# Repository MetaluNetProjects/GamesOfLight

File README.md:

# GamesOfLight
GroupeLAPS - GamesOfLight repository

### Pd externals to install:

- Fraise
- moonlib
- zexy
- ggee
- motex
- iemlib

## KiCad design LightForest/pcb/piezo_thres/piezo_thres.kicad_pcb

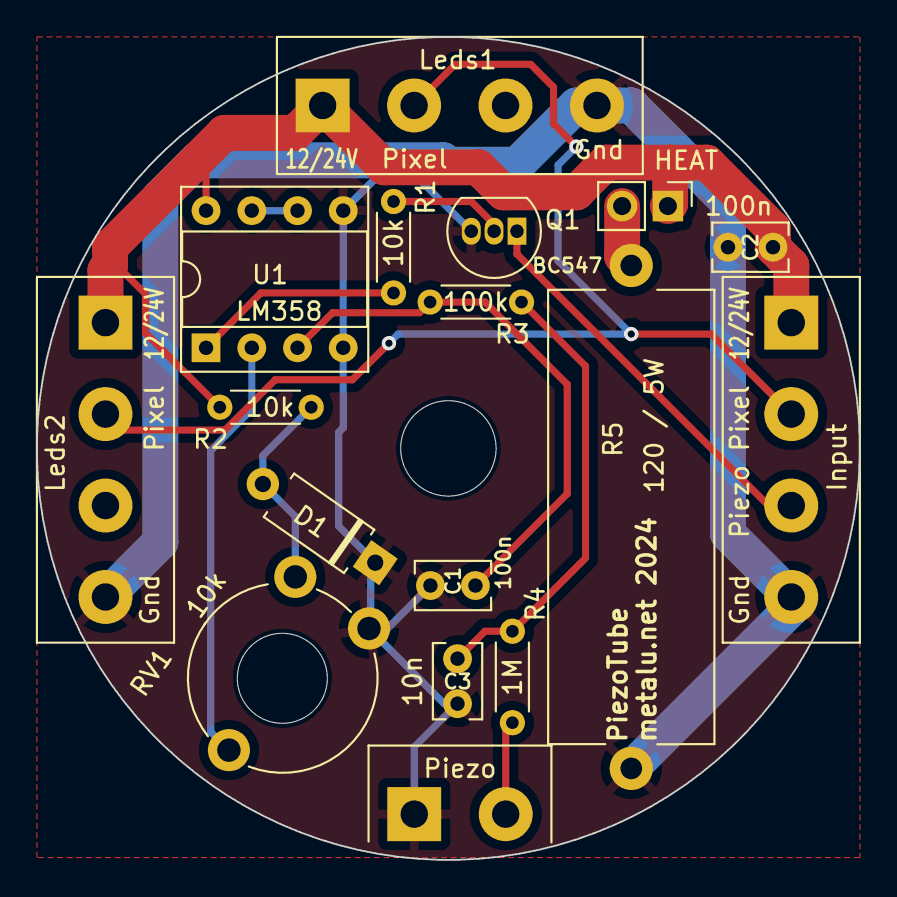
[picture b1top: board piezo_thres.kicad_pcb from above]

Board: 2 copper layers, 45.7 x 45.7 mm, 18 parts (0 on the bottom side), 13 nets.

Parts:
C1, C2: 100n; C_Rect_L4.0mm_W2.5mm_P2.50mm
C3: 10n; C_Rect_L4.0mm_W2.5mm_P2.50mm
D1: D; D_A-405_P7.62mm_Horizontal
H2: MountingHole; MountingHole_5.3mm_M5
HEAT: Conn_01x02_Pin; PinHeader_1x02_P2.54mm_Vertical
J1: Piezo; TerminalBlock_bornier-2_P5.08mm
J2: Input; TerminalBlock_bornier-4_P5.08mm
J3: Leds1; TerminalBlock_bornier-4_P5.08mm
J4: Leds2; TerminalBlock_bornier-4_P5.08mm
Q1: BC547; TO-92_Inline
R1, R2: 10k; R_Axial_DIN0204_L3.6mm_D1.6mm_P5.08mm_Horizontal
R3: 100k; R_Axial_DIN0204_L3.6mm_D1.6mm_P5.08mm_Horizontal
R4: 1M; R_Axial_DIN0204_L3.6mm_D1.6mm_P5.08mm_Horizontal
R5: 120 / 5W; R_Axial_Power_L25.0mm_W9.0mm_P27.94mm
RV1: 10k; Potentiometer_Piher_PT-10-V10_Vertical
U1: LM358; DIP-8_W7.62mm_Socket

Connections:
+24V: C2.1, HEAT.1, J2.1, J3.1, J4.1, R2.1, U1.8 (V+)
/piezo_out: J2.3, Q1.1 (C)
/pixel: J2.2, J3.2, J4.2
GND: C1.2, C2.2, C3.2, D1.1 (K), J1.1, J2.4, J3.4, J4.4, Q1.3 (E), R5.1, RV1.3, U1.4 (V-), U1.5 (+)
unnamed: C3.1, R3.2, R4.1
unnamed: D1.2 (A), R2.2, RV1.1
unnamed: J1.2, R4.2
unnamed: HEAT.2, R5.2
unnamed: Q1.2 (B), R1.2
unnamed: R1.1, U1.1
unnamed: C1.1, R3.1, U1.3 (+)
unnamed: RV1.2, U1.2 (-)
unnamed: U1.6 (-), U1.7

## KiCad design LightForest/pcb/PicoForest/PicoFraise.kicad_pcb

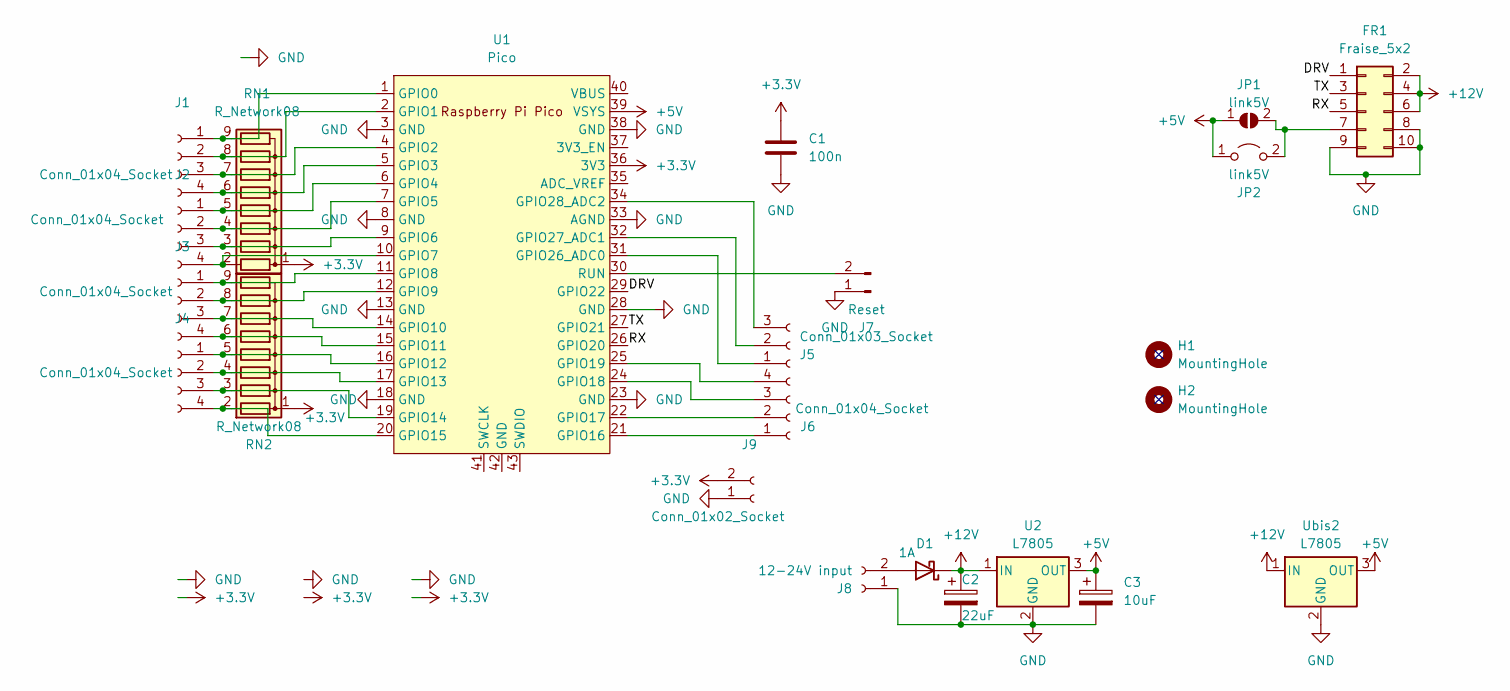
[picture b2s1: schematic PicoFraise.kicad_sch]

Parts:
C1: 100n; C_Rect_L4.0mm_W2.5mm_P2.50mm
C2: 22uF; CP_Radial_D5.0mm_P2.50mm
C3: 10uF; CP_Radial_D5.0mm_P2.50mm
D1: 1A; D_SMA
FR1: Fraise_5x2; IDC-Header_2x05_P2.54mm_Vertical
H1, H2: MountingHole; MountingHole_3.2mm_M3_Pad_TopOnly
J1, J2, J3, J4, J6: Conn_01x04_Socket; TerminalBlock_bornier-4_P5.08mm
J5: Conn_01x03_Socket; TerminalBlock_bornier-3_P5.08mm
J7: Reset; PinHeader_1x02_P2.54mm_Vertical
J8: 12-24V input; TerminalBlock_bornier-2_P5.08mm
J9: Conn_01x02_Socket; TerminalBlock_bornier-2_P5.08mm
JP1: link5V; SolderJumper-2_P1.3mm_Open_RoundedPad1.0x1.5mm
JP2: link5V; TestPoint_2Pads_Pitch2.54mm_Drill0.8mm
RN1, RN2: R_Network08; R_Array_SIP9
U1: Pico; RPi_Pico_SMD_TH
U2: L7805; TO-220-3_Vertical
Ubis2: L7805; TO-252-3_TabPin2

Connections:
+3.3V: C1.1, J9.2, RN1.1 (common), RN2.1 (common), U1.36 (3V3)
+5V: C3.1, JP1.1 (A), JP2.1 (A), U1.39 (VSYS), U2.3 (OUT), Ubis2.3 (OUT)
+12V: C2.1, D1.1 (K), FR1.2, FR1.4, FR1.6, U2.1 (IN), Ubis2.1 (IN)
/DRV: FR1.1, U1.29 (GPIO22)
/RX: FR1.5, U1.26 (GPIO20)
/TX: FR1.3, U1.27 (GPIO21)
GND: C1.2, C2.2, C3.2, FR1.8, FR1.9, FR1.10, J7.1, J8.1, J9.1, U1.3 (GND), U1.8 (GND), U1.13 (GND), U1.18 (GND), U1.23 (GND), U1.28 (GND), U1.33 (AGND), U1.38 (GND), U2.2 (GND), Ubis2.2 (GND)
unnamed: D1.2 (A), J8.2
unnamed: FR1.7, JP1.2 (B), JP2.2 (B)
unnamed: J1.1, RN1.9 (R8), U1.1 (GPIO0)
unnamed: J1.2, RN1.8 (R7), U1.2 (GPIO1)
unnamed: J1.3, RN1.7 (R6), U1.4 (GPIO2)
unnamed: J1.4, RN1.6 (R5), U1.5 (GPIO3)
unnamed: J2.1, RN1.5 (R4), U1.6 (GPIO4)
unnamed: J2.2, RN1.4 (R3), U1.7 (GPIO5)
unnamed: J2.3, RN1.3 (R2), U1.9 (GPIO6)
unnamed: J2.4, RN1.2 (R1), U1.10 (GPIO7)
unnamed: J3.1, RN2.9 (R8), U1.11 (GPIO8)
unnamed: J3.2, RN2.8 (R7), U1.12 (GPIO9)
unnamed: J3.3, RN2.7 (R6), U1.14 (GPIO10)
unnamed: J3.4, RN2.6 (R5), U1.15 (GPIO11)
unnamed: J4.1, RN2.5 (R4), U1.16 (GPIO12)
unnamed: J4.2, RN2.4 (R3), U1.17 (GPIO13)
unnamed: J4.3, RN2.3 (R2), U1.19 (GPIO14)
unnamed: J4.4, RN2.2 (R1), U1.20 (GPIO15)
unnamed: J5.1, U1.31 (GPIO26_ADC0)
unnamed: J5.2, U1.32 (GPIO27_ADC1)
unnamed: J5.3, U1.34 (GPIO28_ADC2)
unnamed: J6.1, U1.21 (GPIO16)
unnamed: J6.2, U1.22 (GPIO17)
unnamed: J6.3, U1.24 (GPIO18)
unnamed: J6.4, U1.25 (GPIO19)
unnamed: J7.2, U1.30 (RUN)

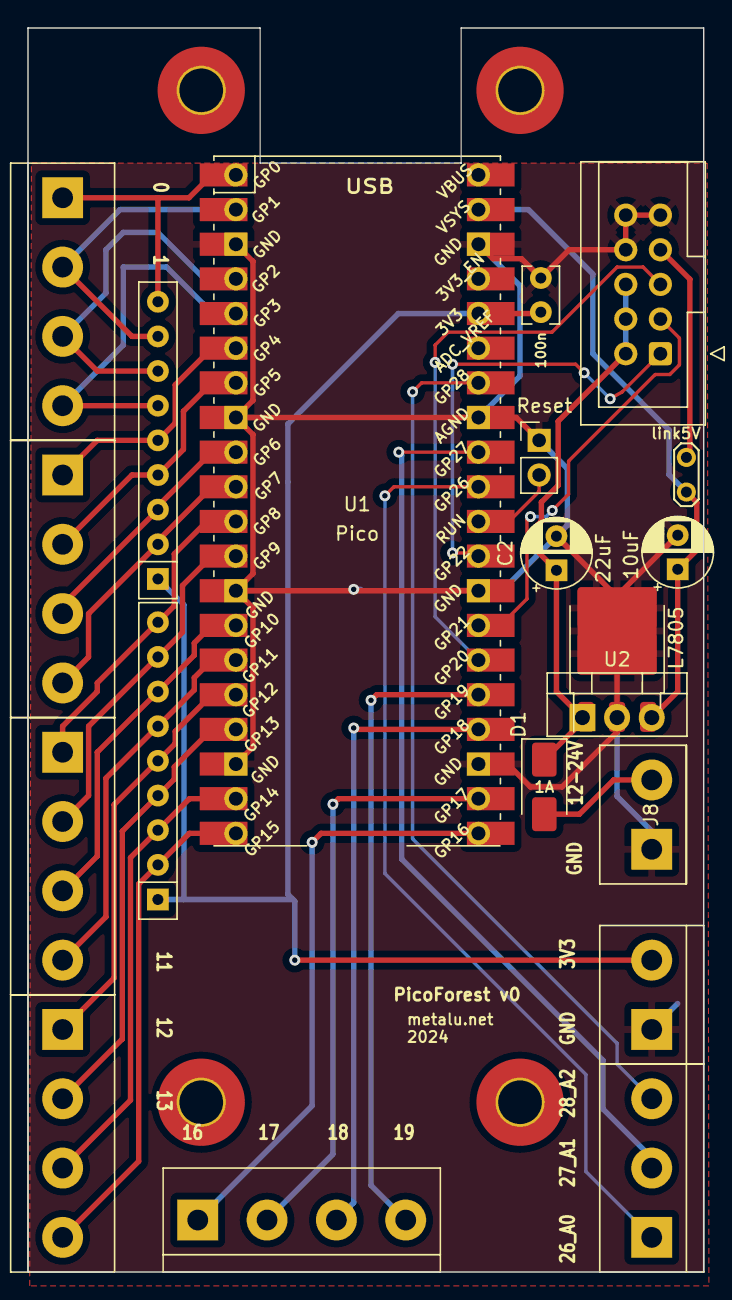
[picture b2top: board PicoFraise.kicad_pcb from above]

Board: 2 copper layers, 49.5 x 91.2 mm, 25 parts (1 on the bottom side), 33 nets.

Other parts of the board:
H1#2, H2#2: MountingHole; MountingHole_3.2mm_M3_Pad_TopOnly

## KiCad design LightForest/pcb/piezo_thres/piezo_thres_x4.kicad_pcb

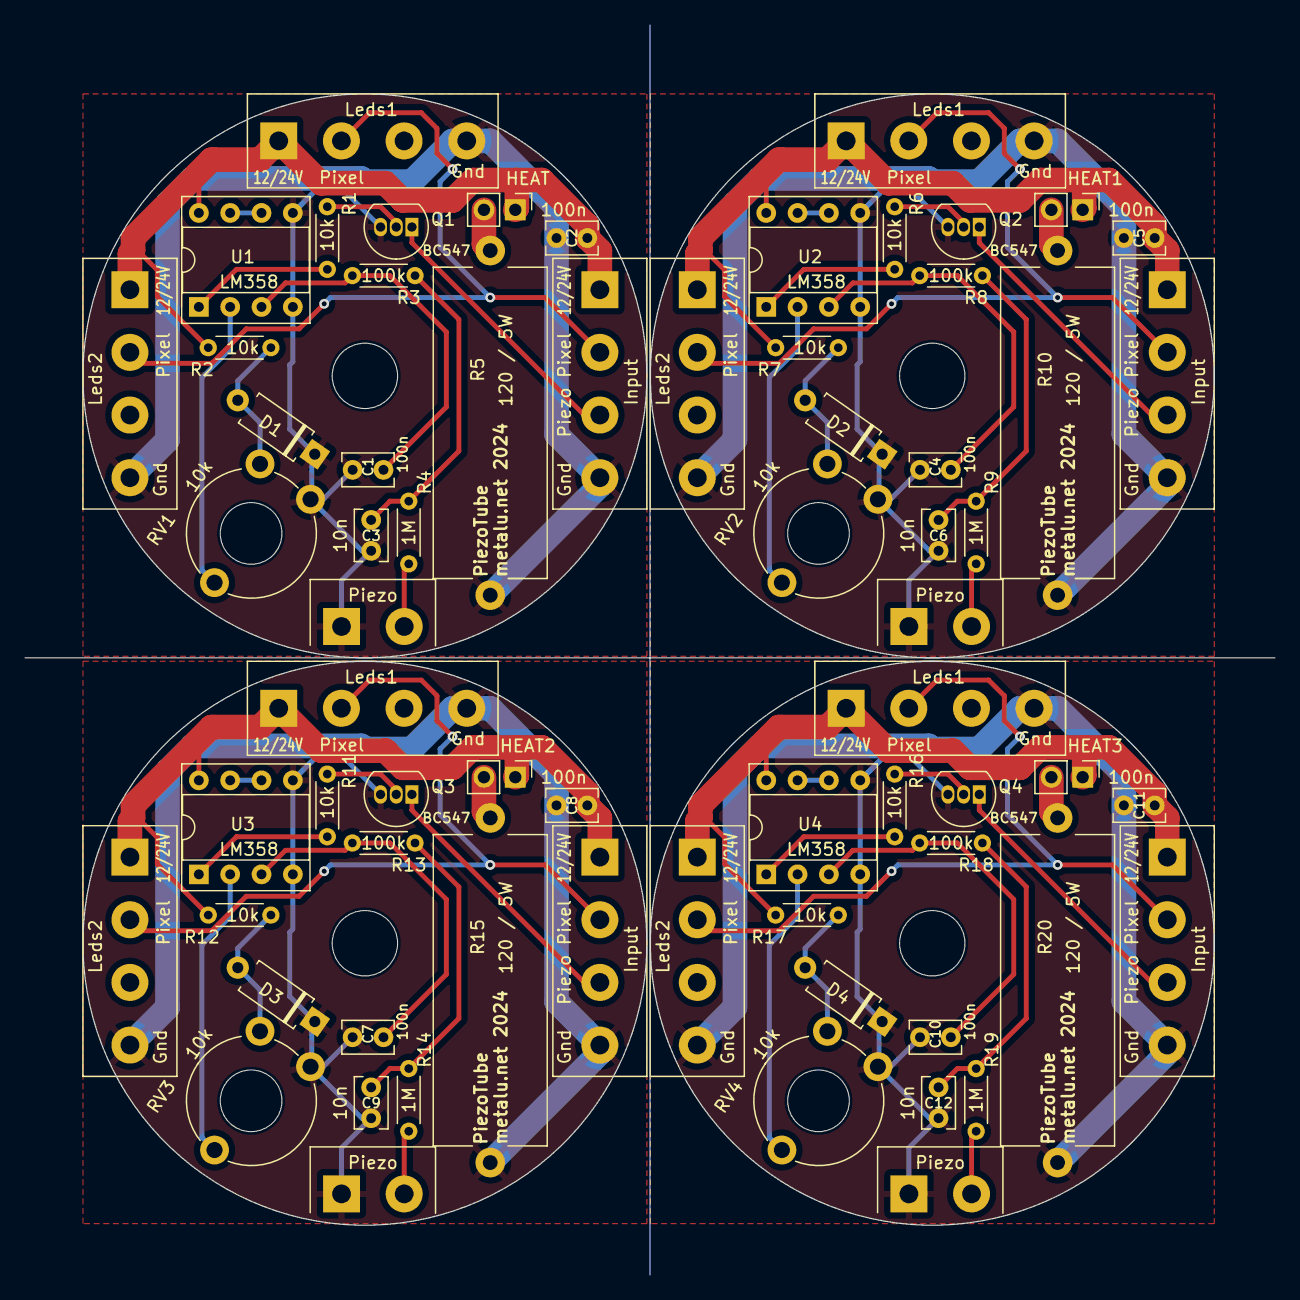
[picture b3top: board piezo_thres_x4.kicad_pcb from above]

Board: 2 copper layers, 101.3 x 101.3 mm, 72 parts (0 on the bottom side), 13 nets.

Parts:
C1, C2, C4, C5, C7, C8, C10, C11: 100n; C_Rect_L4.0mm_W2.5mm_P2.50mm
C3, C6, C9, C12: 10n; C_Rect_L4.0mm_W2.5mm_P2.50mm
D1, D2, D3, D4: D; D_A-405_P7.62mm_Horizontal
H2, H3, H4, H5: MountingHole; MountingHole_5.3mm_M5
HEAT, HEAT1, HEAT2, HEAT3: Conn_01x02_Pin; PinHeader_1x02_P2.54mm_Vertical
J1, J5, J9, J13: Piezo; TerminalBlock_bornier-2_P5.08mm
J2, J6, J10, J14: Input; TerminalBlock_bornier-4_P5.08mm
J3, J7, J11, J15: Leds1; TerminalBlock_bornier-4_P5.08mm
J4, J8, J12, J16: Leds2; TerminalBlock_bornier-4_P5.08mm
Q1, Q2, Q3, Q4: BC547; TO-92_Inline
R1, R2, R6, R7, R11, R12, R16, R17: 10k; R_Axial_DIN0204_L3.6mm_D1.6mm_P5.08mm_Horizontal
R3, R8, R13, R18: 100k; R_Axial_DIN0204_L3.6mm_D1.6mm_P5.08mm_Horizontal
R4, R9, R14, R19: 1M; R_Axial_DIN0204_L3.6mm_D1.6mm_P5.08mm_Horizontal
R5, R10, R15, R20: 120 / 5W; R_Axial_Power_L25.0mm_W9.0mm_P27.94mm
RV1, RV2, RV3, RV4: 10k; Potentiometer_Piher_PT-10-V10_Vertical
U1, U2, U3, U4: LM358; DIP-8_W7.62mm_Socket

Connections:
+24V: C2.1, C5.1, C8.1, C11.1, HEAT.1, HEAT1.1, HEAT2.1, HEAT3.1, J2.1, J3.1, J4.1, J6.1, J7.1, J8.1, J10.1, J11.1, J12.1, J14.1, J15.1, J16.1, R2.1, R7.1, R12.1, R17.1, U1.8 (V+), U2.8 (V+), U3.8 (V+), U4.8 (V+)
/piezo_out: J2.3, J6.3, J10.3, J14.3, Q1.1 (C), Q2.1 (C), Q3.1 (C), Q4.1 (C)
/pixel: J2.2, J3.2, J4.2, J6.2, J7.2, J8.2, J10.2, J11.2, J12.2, J14.2, J15.2, J16.2
GND: C1.2, C2.2, C3.2, C4.2, C5.2, C6.2, C7.2, C8.2, C9.2, C10.2, C11.2, C12.2, D1.1 (K), D2.1 (K), D3.1 (K), D4.1 (K), J1.1, J2.4, J3.4, J4.4, J5.1, J6.4, J7.4, J8.4, J9.1, J10.4, J11.4, J12.4, J13.1, J14.4, J15.4, J16.4, Q1.3 (E), Q2.3 (E), Q3.3 (E), Q4.3 (E), R5.1, R10.1, R15.1, R20.1, RV1.3, RV2.3, RV3.3, RV4.3, U1.4 (V-), U1.5 (+), U2.4 (V-), U2.5 (+), U3.4 (V-), U3.5 (+), U4.4 (V-), U4.5 (+)
unnamed: C3.1, C6.1, C9.1, C12.1, R3.2, R4.1, R8.2, R9.1, R13.2, R14.1, R18.2, R19.1
unnamed: D1.2 (A), D2.2 (A), D3.2 (A), D4.2 (A), R2.2, R7.2, R12.2, R17.2, RV1.1, RV2.1, RV3.1, RV4.1
unnamed: J1.2, J5.2, J9.2, J13.2, R4.2, R9.2, R14.2, R19.2
unnamed: HEAT.2, HEAT1.2, HEAT2.2, HEAT3.2, R5.2, R10.2, R15.2, R20.2
unnamed: Q1.2 (B), Q2.2 (B), Q3.2 (B), Q4.2 (B), R1.2, R6.2, R11.2, R16.2
unnamed: R1.1, R6.1, R11.1, R16.1, U1.1, U2.1, U3.1, U4.1
unnamed: C1.1, C4.1, C7.1, C10.1, R3.1, R8.1, R13.1, R18.1, U1.3 (+), U2.3 (+), U3.3 (+), U4.3 (+)
unnamed: RV1.2, RV2.2, RV3.2, RV4.2, U1.2 (-), U2.2 (-), U3.2 (-), U4.2 (-)
unnamed: U1.6 (-), U1.7, U2.6 (-), U2.7, U3.6 (-), U3.7, U4.6 (-), U4.7

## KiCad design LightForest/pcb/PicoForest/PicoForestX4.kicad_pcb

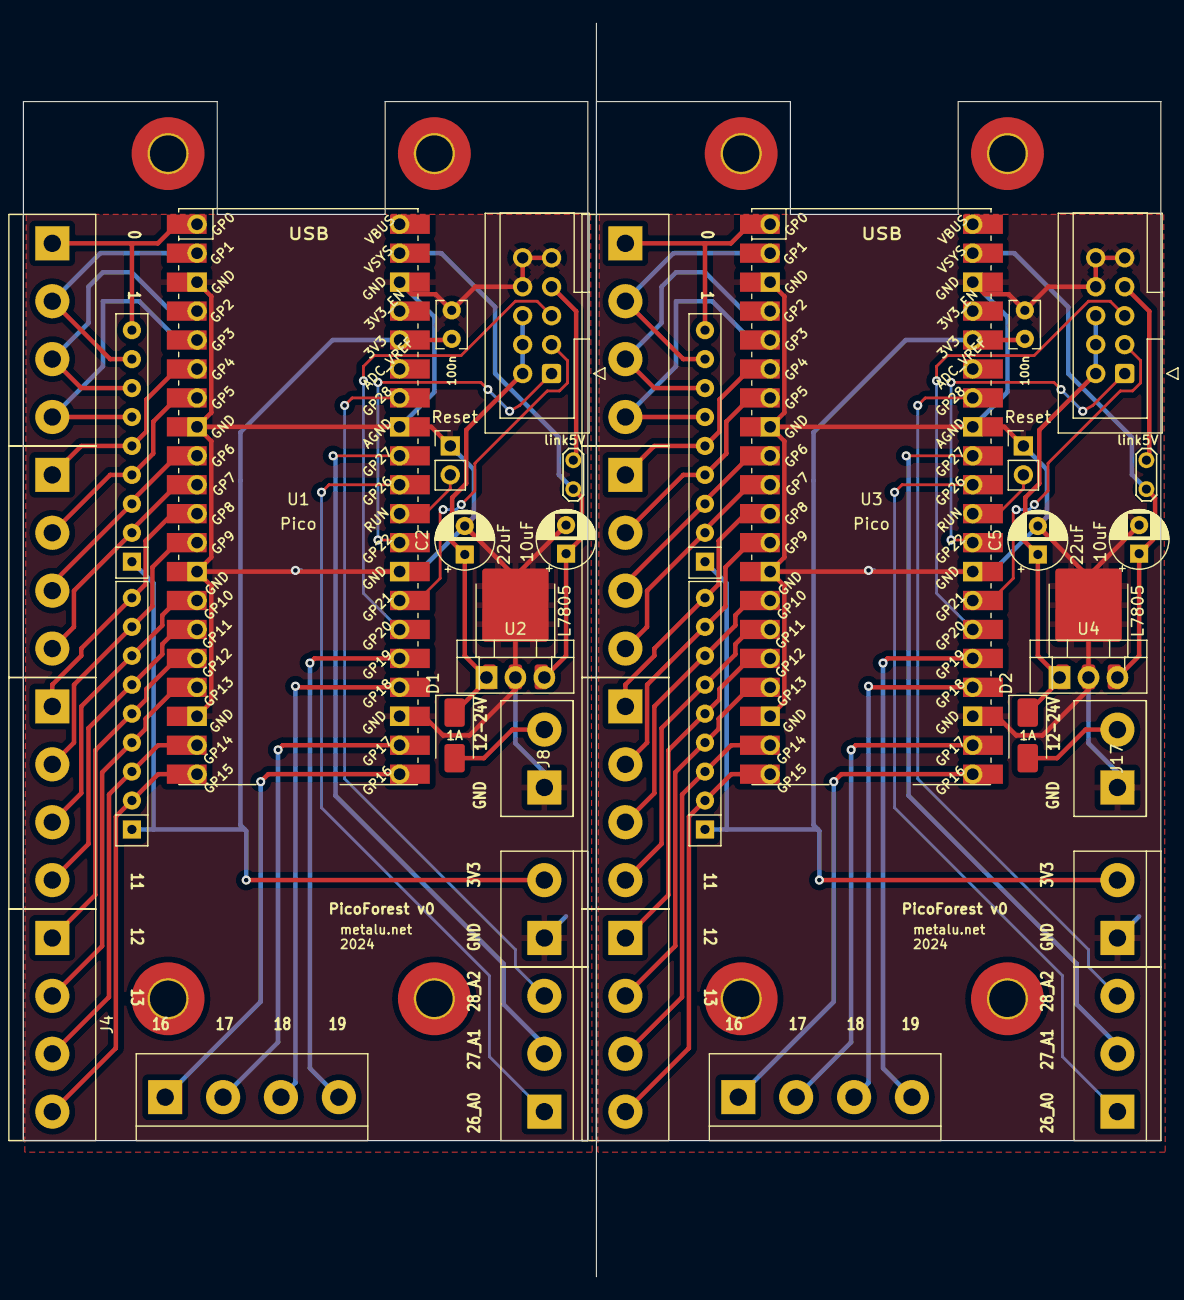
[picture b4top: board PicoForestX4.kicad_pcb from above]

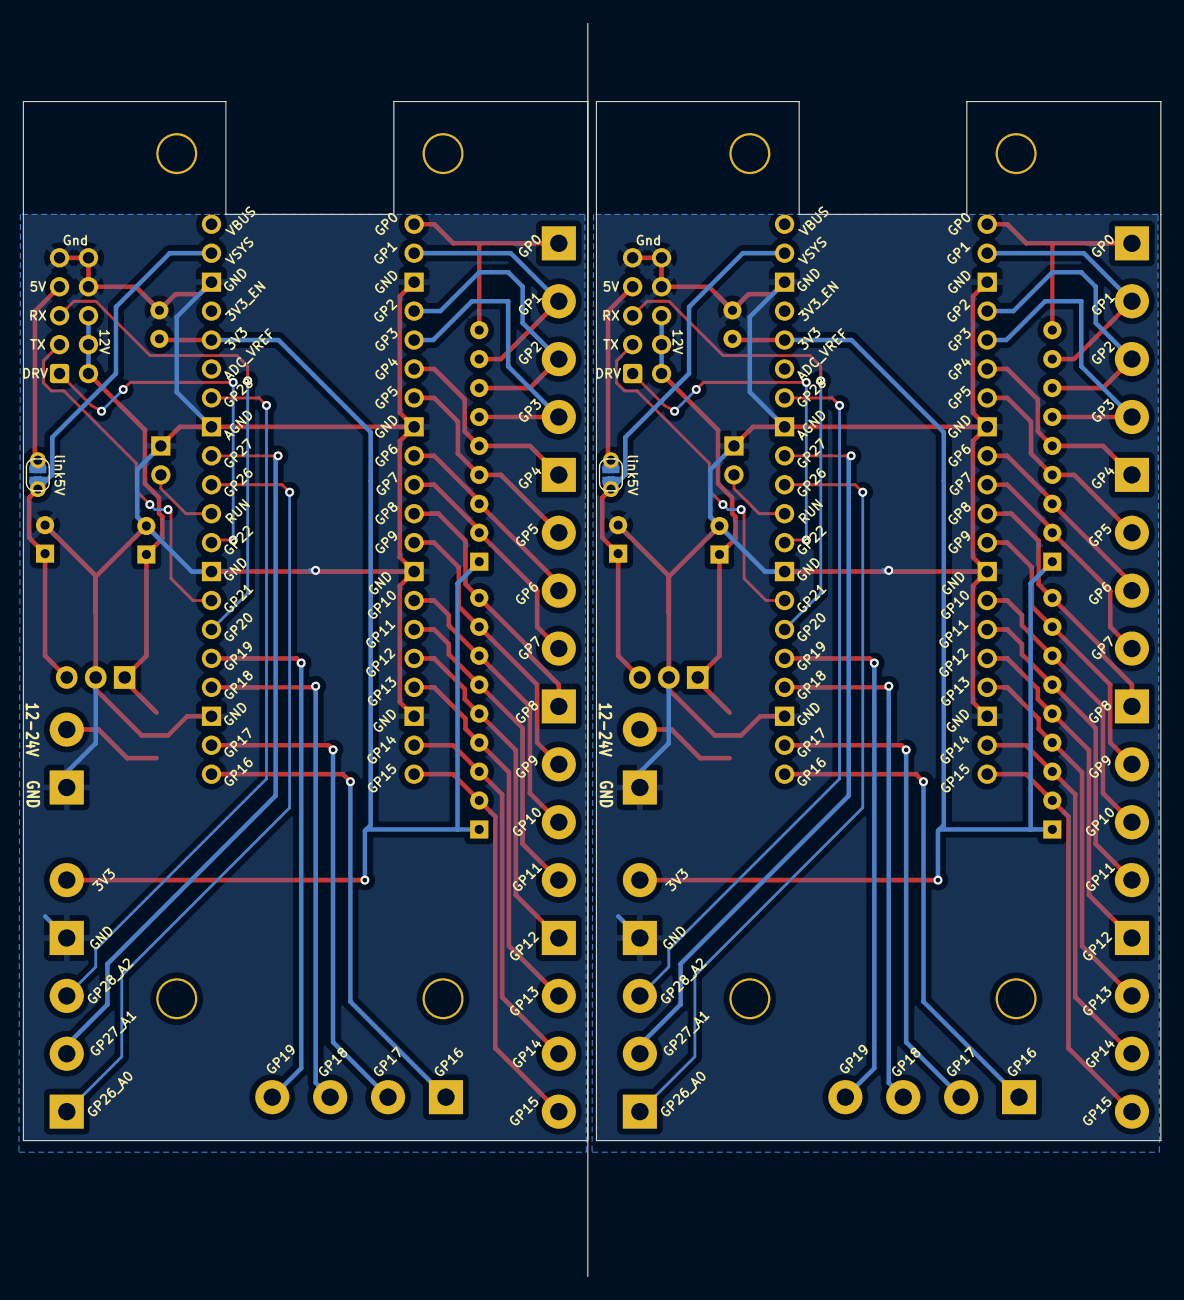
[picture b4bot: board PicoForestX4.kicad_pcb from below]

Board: 2 copper layers, 99.8 x 110.0 mm, 50 parts (2 on the bottom side), 33 nets.

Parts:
C1, C4: 100n; C_Rect_L4.0mm_W2.5mm_P2.50mm
C2, C5: 22uF; CP_Radial_D5.0mm_P2.50mm
C3, C6: 10uF; CP_Radial_D5.0mm_P2.50mm
D1, D2: 1A; D_SMA
FR1, FR2: Fraise_5x2; IDC-Header_2x05_P2.54mm_Vertical
H1, H1#2, H2, H2#2, H3, H4, H5, H6: MountingHole; MountingHole_3.2mm_M3_Pad_TopOnly
J1, J2, J3, J4, J6, J10, J11, J12, J13, J15: Conn_01x04_Socket; TerminalBlock_bornier-4_P5.08mm
J5, J14: Conn_01x03_Socket; TerminalBlock_bornier-3_P5.08mm
J7, J16: Reset; PinHeader_1x02_P2.54mm_Vertical
J8, J17: 12-24V input; TerminalBlock_bornier-2_P5.08mm
J9, J18: Conn_01x02_Socket; TerminalBlock_bornier-2_P5.08mm
JP1, JP3: link5V; SolderJumper-2_P1.3mm_Open_RoundedPad1.0x1.5mm
JP2, JP4: link5V; TestPoint_2Pads_Pitch2.54mm_Drill0.8mm
RN1, RN2, RN3, RN4: R_Network08; R_Array_SIP9
U1, U3: Pico; RPi_Pico_SMD_TH
U2, U4: L7805; TO-220-3_Vertical
Ubis2, Ubis3: L7805; TO-252-3_TabPin2

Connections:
+3.3V: C1.1, C4.1, J9.2, J18.2, RN1.1 (common), RN2.1 (common), RN3.1 (common), RN4.1 (common), U1.36 (3V3), U3.36 (3V3)
+5V: C3.1, C6.1, JP1.1 (A), JP2.1 (A), JP3.1 (A), JP4.1 (A), U1.39 (VSYS), U2.3 (OUT), U3.39 (VSYS), U4.3 (OUT), Ubis2.3 (OUT), Ubis3.3 (OUT)
+12V: C2.1, C5.1, D1.1 (K), D2.1 (K), FR1.2, FR1.4, FR1.6, FR2.2, FR2.4, FR2.6, U2.1 (IN), U4.1 (IN), Ubis2.1 (IN), Ubis3.1 (IN)
/DRV: FR1.1, FR2.1, U1.29 (GPIO22), U3.29 (GPIO22)
/RX: FR1.5, FR2.5, U1.26 (GPIO20), U3.26 (GPIO20)
/TX: FR1.3, FR2.3, U1.27 (GPIO21), U3.27 (GPIO21)
GND: C1.2, C2.2, C3.2, C4.2, C5.2, C6.2, FR1.8, FR1.9, FR1.10, FR2.8, FR2.9, FR2.10, J7.1, J8.1, J9.1, J16.1, J17.1, J18.1, U1.3 (GND), U1.8 (GND), U1.13 (GND), U1.18 (GND), U1.23 (GND), U1.28 (GND), U1.33 (AGND), U1.38 (GND), U2.2 (GND), U3.3 (GND), U3.8 (GND), U3.13 (GND), U3.18 (GND), U3.23 (GND), U3.28 (GND), U3.33 (AGND), U3.38 (GND), U4.2 (GND), Ubis2.2 (GND), Ubis3.2 (GND)
unnamed: D1.2 (A), D2.2 (A), J8.2, J17.2
unnamed: FR1.7, FR2.7, JP1.2 (B), JP2.2 (B), JP3.2 (B), JP4.2 (B)
unnamed: J1.1, J10.1, RN1.9 (R8), RN3.9 (R8), U1.1 (GPIO0), U3.1 (GPIO0)
unnamed: J1.2, J10.2, RN1.8 (R7), RN3.8 (R7), U1.2 (GPIO1), U3.2 (GPIO1)
unnamed: J1.3, J10.3, RN1.7 (R6), RN3.7 (R6), U1.4 (GPIO2), U3.4 (GPIO2)
unnamed: J1.4, J10.4, RN1.6 (R5), RN3.6 (R5), U1.5 (GPIO3), U3.5 (GPIO3)
unnamed: J2.1, J11.1, RN1.5 (R4), RN3.5 (R4), U1.6 (GPIO4), U3.6 (GPIO4)
unnamed: J2.2, J11.2, RN1.4 (R3), RN3.4 (R3), U1.7 (GPIO5), U3.7 (GPIO5)
unnamed: J2.3, J11.3, RN1.3 (R2), RN3.3 (R2), U1.9 (GPIO6), U3.9 (GPIO6)
unnamed: J2.4, J11.4, RN1.2 (R1), RN3.2 (R1), U1.10 (GPIO7), U3.10 (GPIO7)
unnamed: J3.1, J12.1, RN2.9 (R8), RN4.9 (R8), U1.11 (GPIO8), U3.11 (GPIO8)
unnamed: J3.2, J12.2, RN2.8 (R7), RN4.8 (R7), U1.12 (GPIO9), U3.12 (GPIO9)
unnamed: J3.3, J12.3, RN2.7 (R6), RN4.7 (R6), U1.14 (GPIO10), U3.14 (GPIO10)
unnamed: J3.4, J12.4, RN2.6 (R5), RN4.6 (R5), U1.15 (GPIO11), U3.15 (GPIO11)
unnamed: J4.1, J13.1, RN2.5 (R4), RN4.5 (R4), U1.16 (GPIO12), U3.16 (GPIO12)
unnamed: J4.2, J13.2, RN2.4 (R3), RN4.4 (R3), U1.17 (GPIO13), U3.17 (GPIO13)
unnamed: J4.3, J13.3, RN2.3 (R2), RN4.3 (R2), U1.19 (GPIO14), U3.19 (GPIO14)
unnamed: J4.4, J13.4, RN2.2 (R1), RN4.2 (R1), U1.20 (GPIO15), U3.20 (GPIO15)
unnamed: J5.1, J14.1, U1.31 (GPIO26_ADC0), U3.31 (GPIO26_ADC0)
unnamed: J5.2, J14.2, U1.32 (GPIO27_ADC1), U3.32 (GPIO27_ADC1)
unnamed: J5.3, J14.3, U1.34 (GPIO28_ADC2), U3.34 (GPIO28_ADC2)
unnamed: J6.1, J15.1, U1.21 (GPIO16), U3.21 (GPIO16)
unnamed: J6.2, J15.2, U1.22 (GPIO17), U3.22 (GPIO17)
unnamed: J6.3, J15.3, U1.24 (GPIO18), U3.24 (GPIO18)
unnamed: J6.4, J15.4, U1.25 (GPIO19), U3.25 (GPIO19)
unnamed: J7.2, J16.2, U1.30 (RUN), U3.30 (RUN)

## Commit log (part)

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2021-11-24 add Templar project
2021-11-24 Templar: ignore future change in threshold.txt and zeros.txt
2021-11-24 add Line4 project
2021-11-24 rename Templar main patch
2021-11-24 add Trampo project
2021-11-26 Templar: move OSC stuff to send_OSC abstraction
2021-11-26 make firmware threshold and debounce times settable from Pd
2021-11-26 finish Trampo (OSC still to be done)
2021-11-26 add Marelle project
2021-11-26 add Snake project
2021-12-01 fix Marelle title...
2021-12-01 add Arbre project (TODO: send_OSC)
2021-12-01 document Pd external libs dependencies
2021-12-01 change old 'declare -stdpath' with 'declare -path'
2021-12-01 add Fraise to README
2021-12-01 Snake: finish send_OSC
2021-12-01 Snake: add test OSC receiver
2021-12-01 Trampo: finish send_OSC
2021-12-01 Marelle: git-ignore configs
2021-12-01 Marelle: finish send_OSC (to be confirmed)
2021-12-02 Templar: change send_OSC to send '/btn [INT(1-5)]' when a hand is detected by the INTth sensor
2021-12-06 add 'impact' detection
2021-12-06 update send_OSC
2021-12-06 Arbre updates
2021-12-07 Marelle: change send_OSC to also send key release
2021-12-07 update Arbre OSC
2021-12-08 Templar: add monitor/test 'On' buttons, and update OSC protocol
2021-12-09 Trampo: send maxValue of last 100ms, and adapt OSC accordingly
2022-07-01 Snake: implement zeros/threshold for new sensors
2022-11-15 Trampo: change to threshold/zero behavior, and disable the trampo1 fruit
2022-11-15 add LightReflex
2022-11-16 bug fix (spurious spaces)
2022-11-25 Arbre: merge mic3 and mic4
2022-11-25 [templar] add software-poweroff in firmware
2022-11-25 [templar] switch off lidars when no activity detected (e.g lidars "crashed"...)
    save the number of lidar reboots to disk for memory.
2022-11-25 [templar] add disconnection_count monitor, and don't listen to the fruit while lidar power is off
2022-11-26 Arbre: update OSC ouput formatting, and add test OSC receiver patch
2022-12-10 implement up/down speed for 'juste' and 'force' filters
2024-06-16 new LightForest project
2024-06-26 add send_OSC to LightForset, and add TemplarLaser, Machines and LightReflex2
2024-07-01 light forest: decrease fw debounce timeout from 40ms to 10ms
2024-07-02 lightreflex2: decrease debounce time down to 10ms, and add audio test in patch
2024-07-02 Machines: compute encoder speed and send to OSC, and decrease buttons debounce timeout down to 10ms; also add audio test in patch
2024-07-02 TemplarLaser: decrease debounce time down to 10ms, and add audio test in patch
2024-07-02 add colored test buttons (LightForest, LightReflex2, Machines, TemplarLaser)
2024-07-11 use /btn_on and /btn_off in send_OSC for LightForest, LightReflex2, Machines and TemplarLaser
2024-07-17 TemplarLaser: send OSC to a second port for MadMapper
2024-07-17 Machines: send wheel OSC accordingly to Kevin's request
2024-07-22 add Snake_Clockwise
2024-07-22 Machines: add test encoder gui
2024-07-22 bug fix in Machines/send_OSC.pd
2024-08-31 LightForest: forward OSC to port 8001
2024-08-31 LightForest: add a in->out matrix
2024-09-30 LightForest: remove software pullups (since there are now hardware ones)
2024-10-04 piezo thres: add screenshots
2024-10-29 new Dynamo project
2024-11-04 add Buzzer debugging abstraction
2024-11-04 new Spider Hunt project
2024-11-08 Dynamo: make audio layer
2024-11-08 fix wavdirs bang flashing
2024-11-08 import rev3~
2024-11-08 add audioOn feature, listening from OSC
2024-11-09 Dynamo: fix OSC receiving
2024-11-13 Dynamo: fix ambiance volume 'to main' (did wrongly depend on 'dynamos' volume)
2024-11-13 Dynamo: - parametrize phase->vidange range (default 0.5-2.5) - add 'event' feature: OSC message '/event NUM_DYNAMO NUM_WAV' will read file event/NUM_WAV.wav to out channel of dynamaudio NUM_DYNAMO
2024-11-13 Dynamo: add OSC test patch (send/receive)
2024-11-21 dynamos wavfile: bugfix (missing cast to list) and initialize samplerate, length and marks to avoid 0-delay loops
2025-11-05 add tools/scheduler
2025-11-05 add a scheduler to Dynamos
2025-11-22 Arbre: rename send_OSC.pd->send_OSC_Arbre.pd, and split out Resolume part, as send_OSC_Arbre_Resolume.pd
